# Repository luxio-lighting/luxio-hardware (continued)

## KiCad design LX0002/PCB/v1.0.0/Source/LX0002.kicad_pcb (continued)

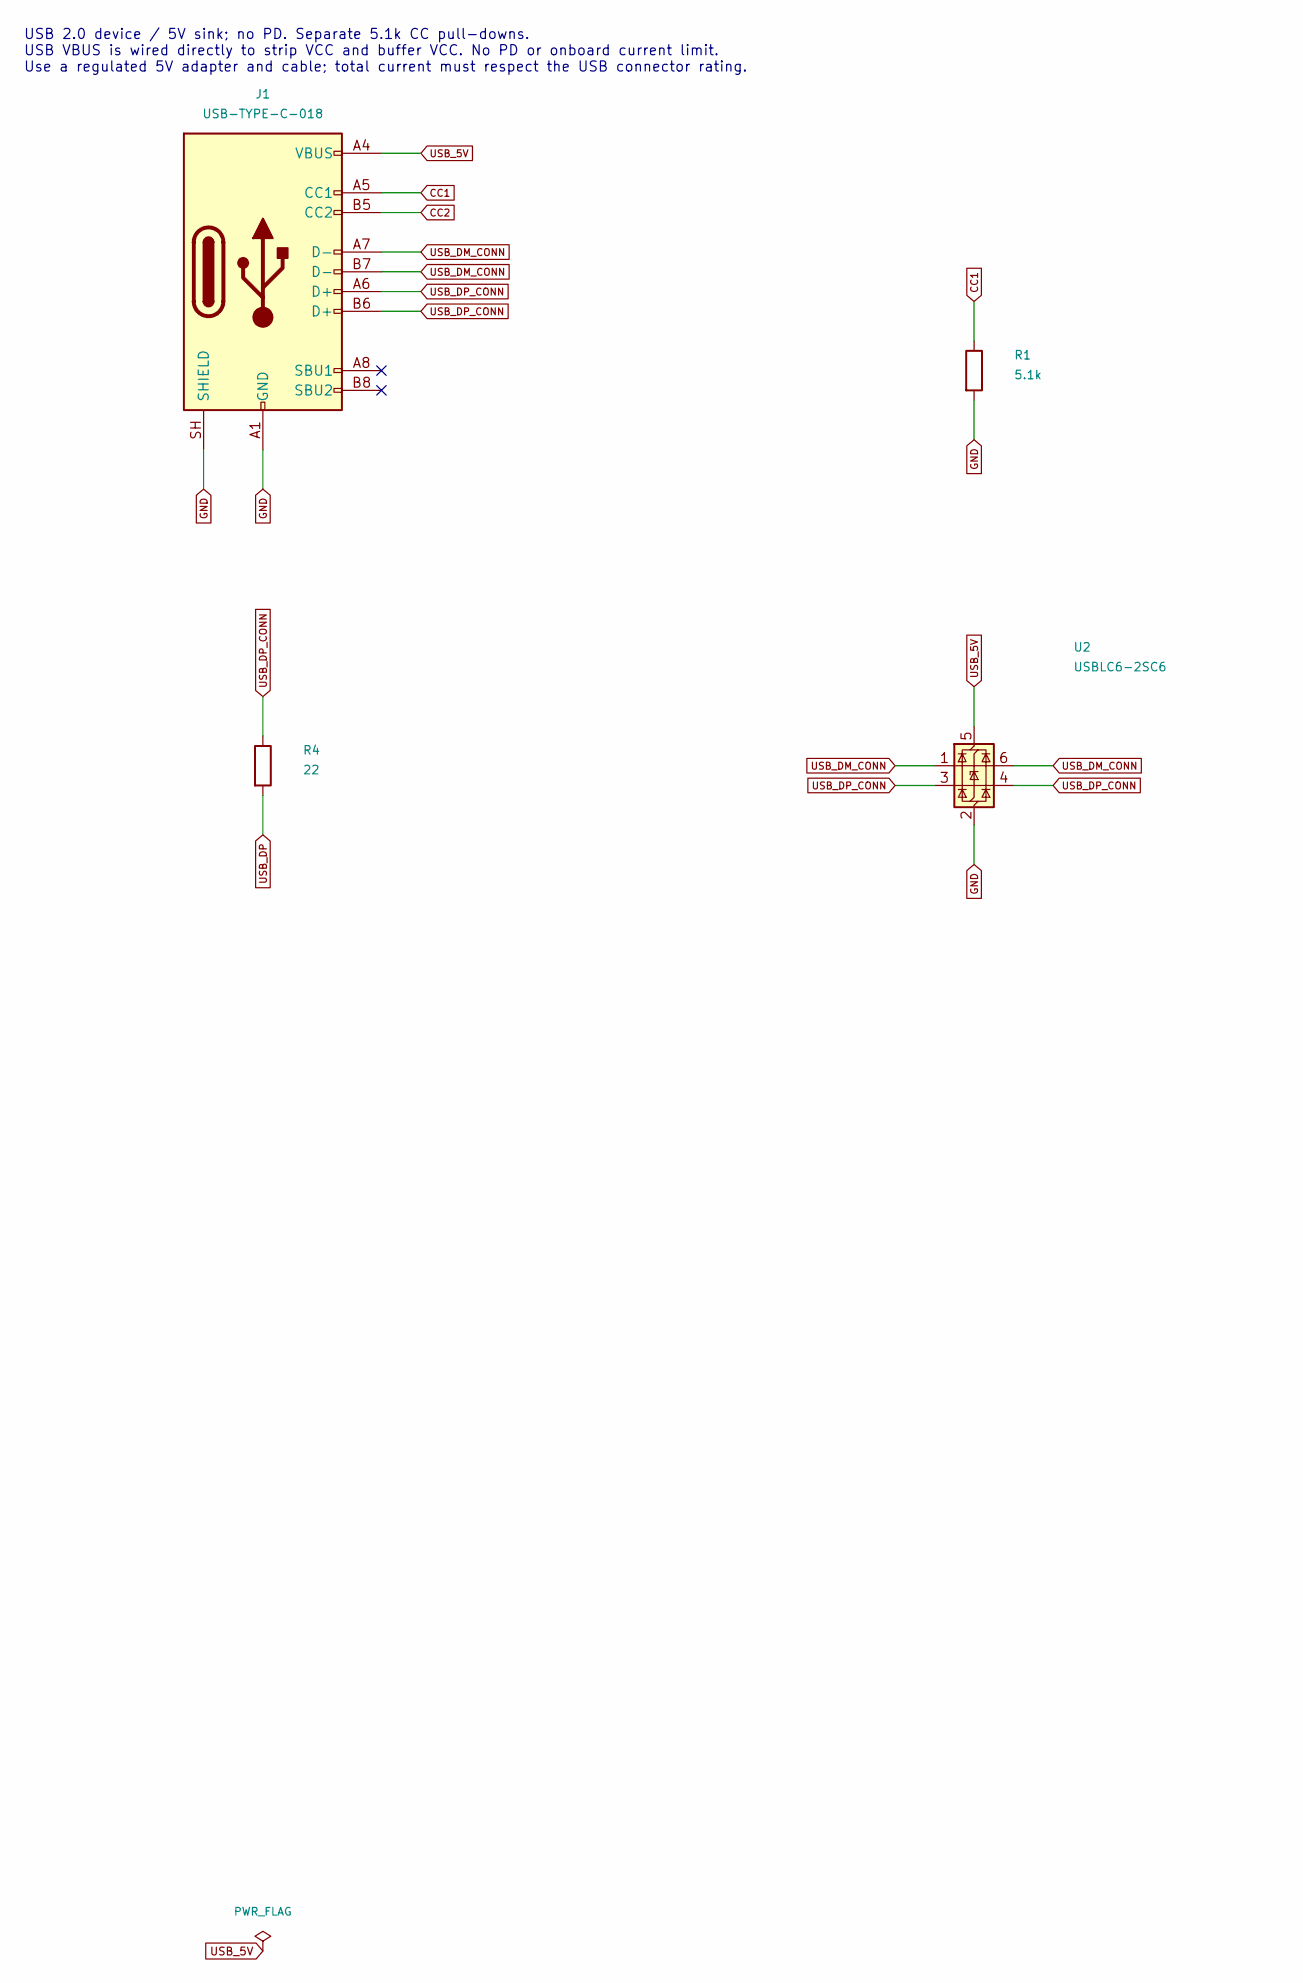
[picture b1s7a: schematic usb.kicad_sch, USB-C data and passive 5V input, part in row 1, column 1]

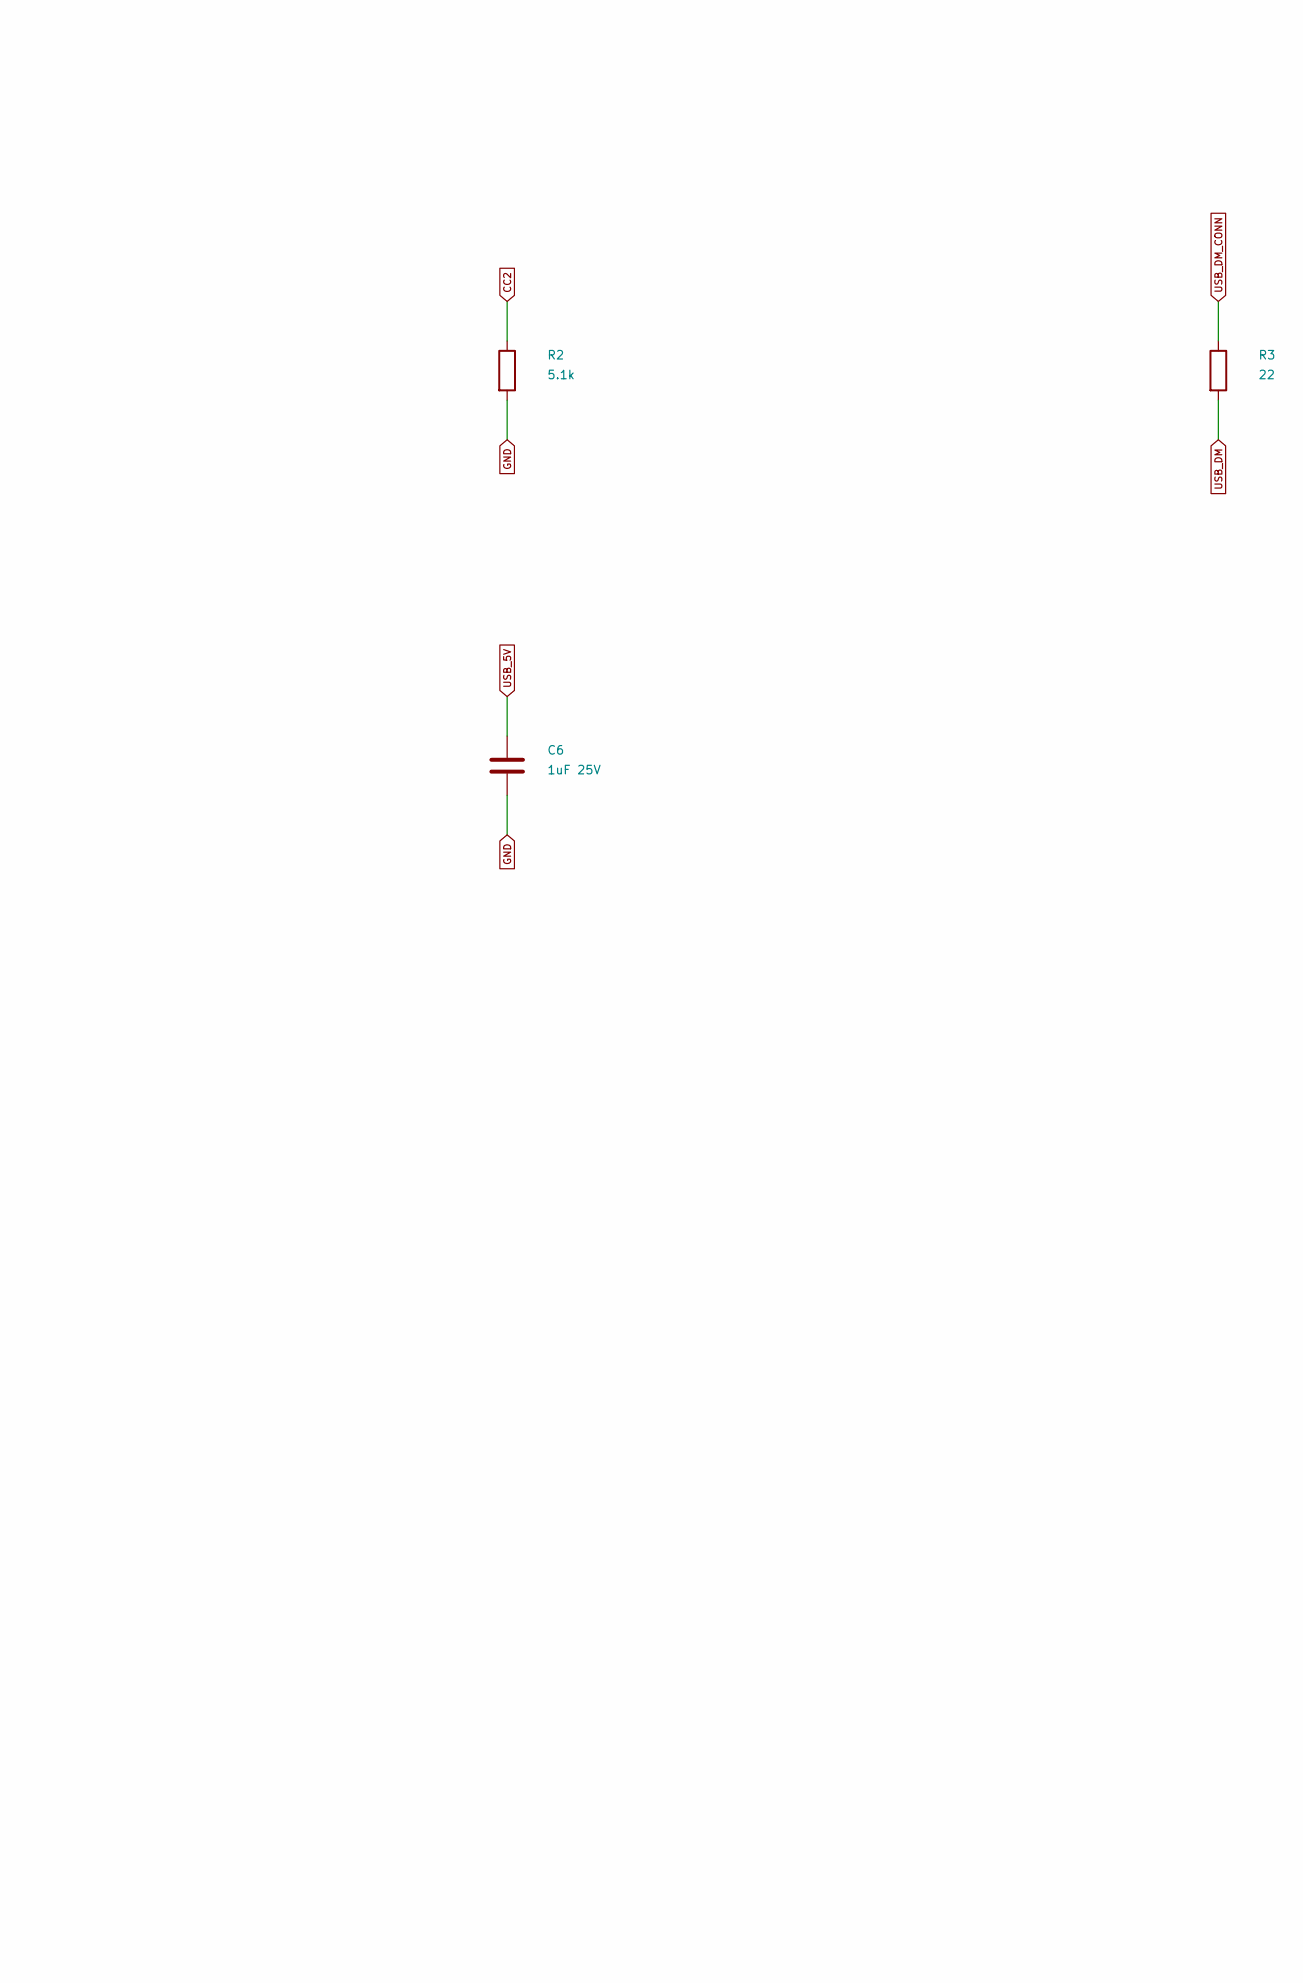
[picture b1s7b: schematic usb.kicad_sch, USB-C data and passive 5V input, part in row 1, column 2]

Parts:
C6: 1uF 25V; C_0402_1005Metric; LCSC C52923
J1: USB-TYPE-C-018; USB_C_DEALON_USB_TYPE_C_018; LCSC C2927038
R1, R2: 5.1k; R_0402_1005Metric; LCSC C25905
R3, R4: 22; R_0402_1005Metric; LCSC C25092
U2: USBLC6-2SC6; SOT-23-6; LCSC C7519

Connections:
CC1: J1.A5 (CC1), R1.1
CC2: J1.B5 (CC2), R2.1
GND: C6.2, J1.A1 (GND), J1.A12 (GND), J1.B1 (GND), J1.B12 (GND), J1.SH (SHIELD), R1.2, R2.2, U2.2 (GND); also elsewhere on the board
USB_5V: C6.1, J1.A4 (VBUS), J1.A9 (VBUS), J1.B4 (VBUS), J1.B9 (VBUS), U2.5 (VBUS); also elsewhere on the board
USB_DM: R3.2; also elsewhere on the board
USB_DM_CONN: J1.A7 (D-), J1.B7 (D-), R3.1, U2.1 (I/O1), U2.6 (I/O1)
USB_DP: R4.2; also elsewhere on the board
USB_DP_CONN: J1.A6 (D+), J1.B6 (D+), R4.1, U2.3 (I/O2), U2.4 (I/O2)

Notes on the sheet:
USB 2.0 device / 5V sink; no PD. Separate 5.1k CC pull-downs. USB VBUS is wired directly to strip VCC and buffer VCC. No PD or onboard current limit. Use a regulated 5V adapter and cable; total current must respect the USB connector rating.

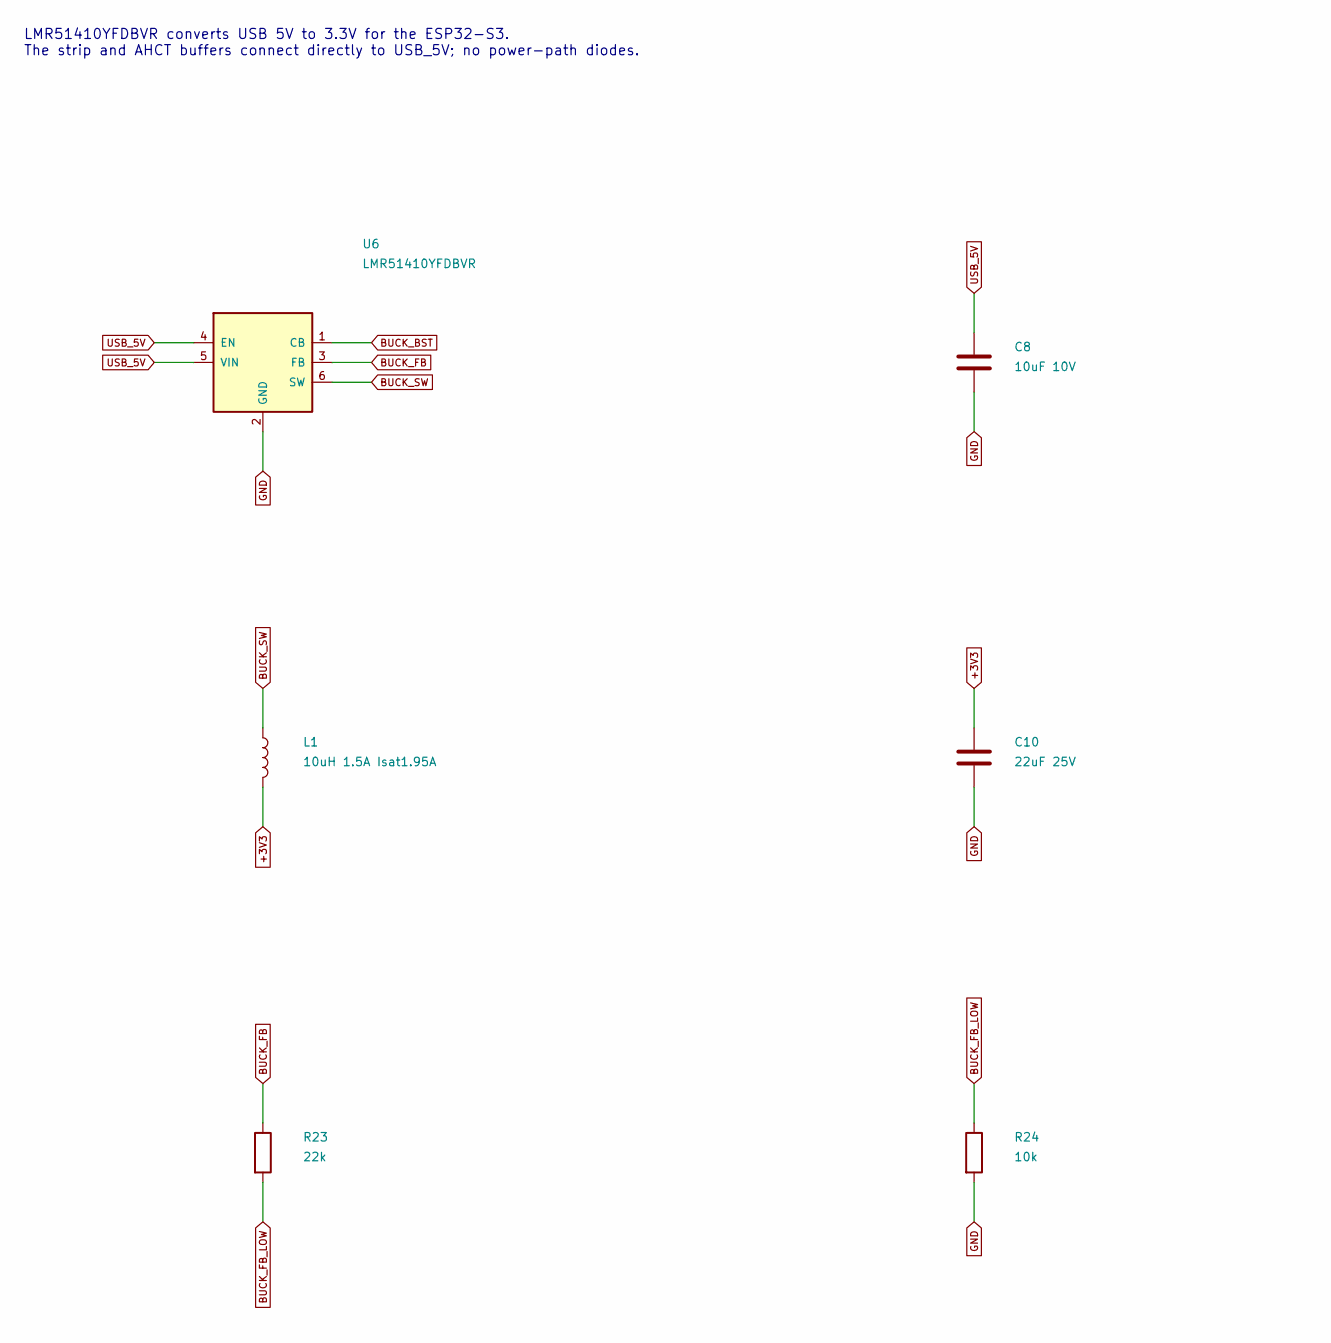
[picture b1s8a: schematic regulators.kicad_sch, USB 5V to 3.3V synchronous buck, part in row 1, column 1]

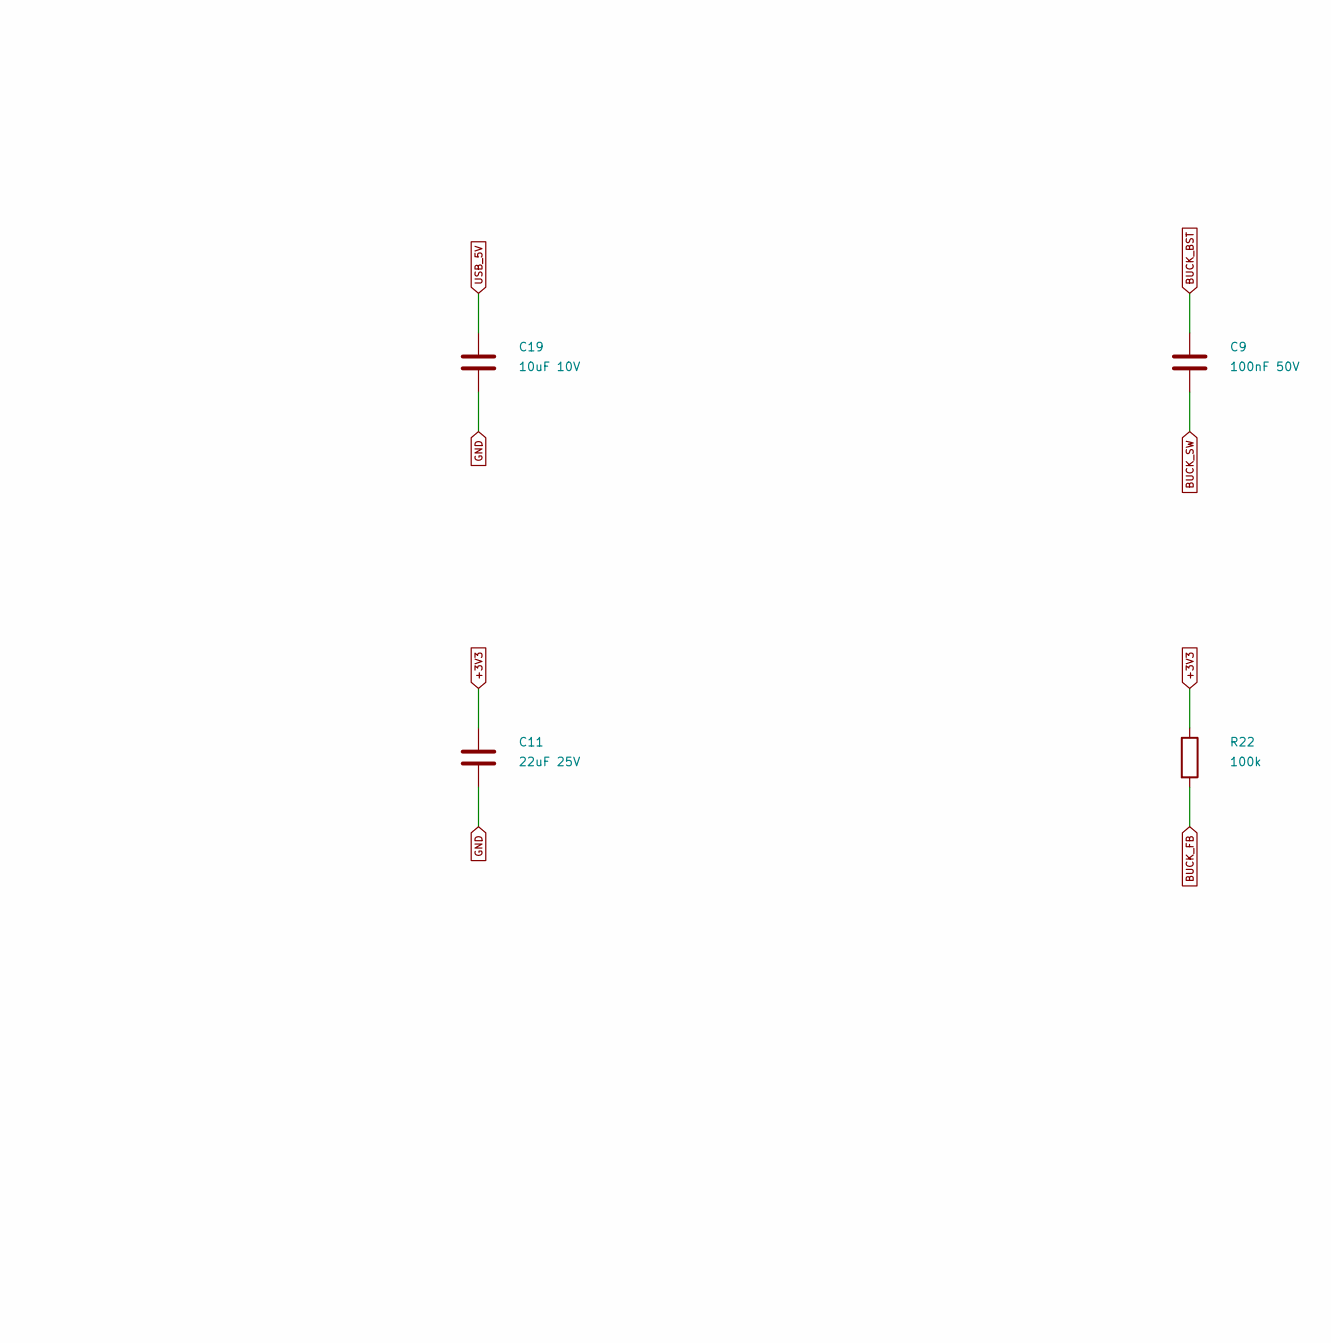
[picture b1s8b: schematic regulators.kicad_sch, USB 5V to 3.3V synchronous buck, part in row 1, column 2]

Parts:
C8, C19: 10uF 10V; C_0603_1608Metric; LCSC C19702
C9: 100nF 50V; C_0603_1608Metric; LCSC C14663
C10, C11: 22uF 25V; C_0805_2012Metric; LCSC C45783
L1: 10uH 1.5A Isat1.95A; L_Sunlord_SWPA4030S; LCSC C38117
R22: 100k; R_0402_1005Metric; LCSC C25741
R23: 22k; R_0402_1005Metric; LCSC C25768
R24: 10k; R_0402_1005Metric; LCSC C25744
U6: LMR51410YFDBVR; SOT-23-6; LCSC C32347484

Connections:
+3V3: C10.1, C11.1, L1.2, R22.1; also elsewhere on the board
BUCK_BST: C9.1, U6.1 (CB)
BUCK_FB: R22.2, R23.1, U6.3 (FB)
BUCK_FB_LOW: R23.2, R24.1
BUCK_SW: C9.2, L1.1, U6.6 (SW)
GND: C8.2, C10.2, C11.2, C19.2, R24.2, U6.2 (GND); also elsewhere on the board
USB_5V: C8.1, C19.1, U6.4 (EN), U6.5 (VIN); also elsewhere on the board

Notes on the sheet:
LMR51410YFDBVR converts USB 5V to 3.3V for the ESP32-S3. The strip and AHCT buffers connect directly to USB_5V; no power-path diodes.

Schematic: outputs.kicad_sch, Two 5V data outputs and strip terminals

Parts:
C14, C17: 100nF 50V; C_0603_1608Metric; LCSC C14663
J3, J4: 2060-452-HDGC; HDGC_2060_452; LCSC C55251566
R16, R27: 100; R_0603_1608Metric; LCSC C22775
R18, R29: 100k; R_0603_1608Metric; LCSC C25803
U8, U9: SN74AHCT1G125DBVR; SOT-23-5; LCSC C7484

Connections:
DATA16_5V: R16.1, U8.4
DATA16_OUT: J3.1, R16.2
DATA17_5V: R27.1, U9.4
DATA17_OUT: J4.2, R27.2
GND: C14.2, C17.2, J3.2, R18.2, R29.2, U8.1, U8.3 (GND), U9.1, U9.3 (GND); also elsewhere on the board
GPIO16: R18.1, U8.2; also elsewhere on the board
GPIO17: R29.1, U9.2; also elsewhere on the board
USB_5V: C14.1, C17.1, J4.1, U8.5 (VCC), U9.5 (VCC); also elsewhere on the board

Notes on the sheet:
GPIO16 / GPIO17 -> AHCT buffers -> 100-ohm series resistors. Buffers always enabled in hardware; 100k input pull-downs hold data low during reset.

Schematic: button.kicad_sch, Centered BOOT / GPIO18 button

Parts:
D4: BAT54C; SOT-23; LCSC C2135
R30: 10k; R_0402_1005Metric; LCSC C25744
SW1: TS-1088-AR02016; SW_TS-1088-AR02016; LCSC C720477

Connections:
+3V3: R30.1; also elsewhere on the board
BOOT: D4.1; also elsewhere on the board
BUTTON_COMMON: D4.3, SW1.1
GND: SW1.2; also elsewhere on the board
GPIO18_BUTTON: D4.2, R30.2; also elsewhere on the board

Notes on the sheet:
SW1 pulls BOOT and GPIO18 low through separate Schottky diodes. Firmware uses GPIO18 as an input. BOOT must be held low during reset for download.

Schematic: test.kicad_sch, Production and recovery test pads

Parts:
TP1: GND; TestPoint_Pad_D1.0mm
TP2: +3V3; TestPoint_Pad_D1.0mm
TP3: ESP_EN; TestPoint_Pad_D0.5mm
TP6: GPIO16; TestPoint_Pad_D1.0mm
TP7: GPIO17; TestPoint_Pad_D1.0mm
TP8, TP9: USB_5V; TestPoint_Pad_D1.0mm
TP10: GPIO18_BUTTON; TestPoint_Pad_D1.0mm

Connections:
+3V3: TP2.1; also elsewhere on the board
ESP_EN: TP3.1; also elsewhere on the board
GND: TP1.1; also elsewhere on the board
GPIO16: TP6.1; also elsewhere on the board
GPIO17: TP7.1; also elsewhere on the board
GPIO18_BUTTON: TP10.1; also elsewhere on the board
USB_5V: TP8.1, TP9.1; also elsewhere on the board

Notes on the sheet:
Test-point map for recovery, power rails and data. Use common ground. Data buffers are always enabled; no power-control GPIOs.

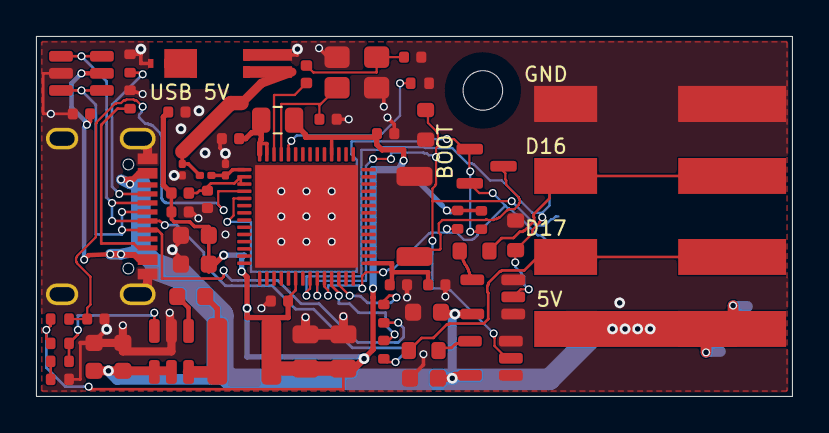
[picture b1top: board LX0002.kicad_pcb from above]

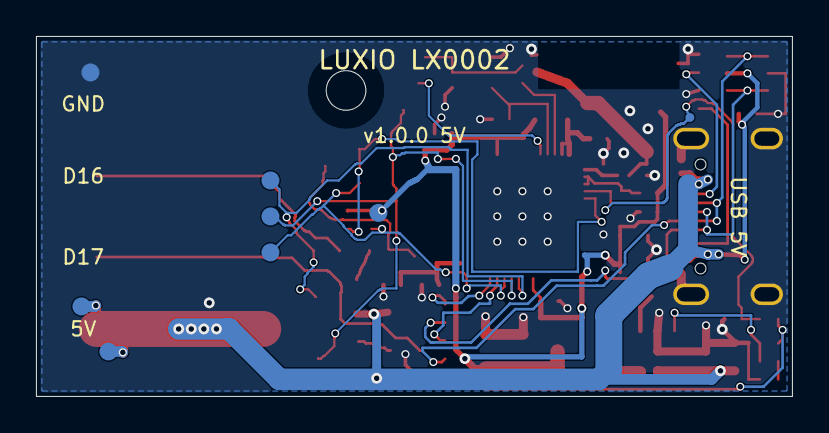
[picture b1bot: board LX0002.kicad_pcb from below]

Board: 2 copper layers, 42.0 x 20.0 mm, 65 parts (8 on the bottom side), 33 nets.

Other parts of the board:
H2: MountingHole_2.2mm_M2

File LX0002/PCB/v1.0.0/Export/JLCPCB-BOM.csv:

Comment,Designator,Footprint,LCSC Part #,Quantity
RFECA3216060A1T,ANT1,Core:Walsin_RFECA3216060A1T_Type1,C127620,1
100nF 50V,"C14,C17,C9",Capacitor_SMD:C_0603_1608Metric,C14663,3
100nF 16V,"C101,C102,C103,C104,C105,C108",Capacitor_SMD:C_0402_1005Metric,C1525,6
18pF 50V C0G,"C112,C113",Capacitor_SMD:C_0402_1005Metric,C1549,2
1.5pF 50V C0G,"C114,C115",Capacitor_SMD:C_0201_0603Metric,C161414,2
0,R106,Resistor_SMD:R_0805_2012Metric,C17477,1
2nH 900mA,L100,Inductor_SMD:L_0402_1005Metric,C18216,1
10uF 10V,"C100,C107,C19,C8",Capacitor_SMD:C_0603_1608Metric,C19702,4
BAT54C,D4,Package_TO_SOT_SMD:SOT-23,C2135,1
100,"R16,R27",Resistor_SMD:R_0603_1608Metric,C22775,2
22,"R3,R4",Resistor_SMD:R_0402_1005Metric,C25092,2
100k,R22,Resistor_SMD:R_0402_1005Metric,C25741,1
10k,"R100,R101,R103,R24,R30",Resistor_SMD:R_0402_1005Metric,C25744,5
22k,R23,Resistor_SMD:R_0402_1005Metric,C25768,1
100k,"R18,R29",Resistor_SMD:R_0603_1608Metric,C25803,2
5.1k,"R1,R2",Resistor_SMD:R_0402_1005Metric,C25905,2
USB-TYPE-C-018,J1,LX0002:USB_C_DEALON_USB_TYPE_C_018,C2927038,1
ESP32-S3FH4R2,U1,Core:ESP32_S3FH4R2_QFN56_7x7_EP5p7,C3013940,1
LMR51410YFDBVR,U6,Package_TO_SOT_SMD:SOT-23-6,C32347484,1
10uH 1.5A Isat1.95A,L1,Inductor_SMD:L_Sunlord_SWPA4030S,C38117,1
22uF 25V,"C10,C11",Capacitor_SMD:C_0805_2012Metric,C45783,2
1uF 25V,"C106,C109,C111,C6",Capacitor_SMD:C_0402_1005Metric,C52923,4
2060-452-HDGC,"J3,J4",LX0002:HDGC_2060_452,C55251566,2
40MHz 12pF 10ppm,Y1,Crystal:Crystal_SMD_3225-4Pin_3.2x2.5mm,C655034,1
TS-1088-AR02016,SW1,LX0002:SW_TS-1088-AR02016,C720477,1
2.7nH,L102,Inductor_SMD:L_0201_0603Metric,C7216765,1
SN74AHCT1G125DBVR,"U8,U9",Package_TO_SOT_SMD:SOT-23-5,C7484,2
USBLC6-2SC6,U2,Package_TO_SOT_SMD:SOT-23-6,C7519,1
24nH,L101,Inductor_SMD:L_0402_1005Metric,C913699,1

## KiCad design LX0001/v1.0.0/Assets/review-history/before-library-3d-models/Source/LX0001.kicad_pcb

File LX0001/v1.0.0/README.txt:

LX0001 v1.0.0 — Luxio digital LED-strip controller

CURRENT STATUS: Four-layer fabrication data checked; first article not yet built.
Zero unrouted connections, zero schematic parity issues and zero ERC findings.
Four documented mechanical flags concern the recessed USB shell stakes.

Open Source/LX0001.kicad_pro in KiCad 10. The schematic and PCB are editable;
their symbol and footprint libraries are included in Source/libraries.
Custom connector/antenna 3D bodies are approximate preview models. Use the
manufacturer drawings, not the simplified bodies, for enclosure tolerances.

Design
60 x 20 mm, four copper layers, 1.6 mm FR-4, black mask and white silkscreen.
Bare ESP32-S3, 4 MB external flash, no PSRAM, ceramic 2.4 GHz edge antenna.
Two AHCT buffers translate GPIO16 and GPIO17 to 5 V data outputs.
The input terminal and underside USB-C share the end's y=10 mm centerline.
The two output terminals are centered as a pair at the opposite end.
The BOOT/GPIO18 button is centered at (30,10) mm. Two 2.2 mm M2 holes provide
case mounting; their centers are (9,17) and (42,3) mm from the top-left corner.

Connections, viewed from the top with the input at the left
Input, from antenna-side edge toward the opposite edge: GND, 5-24 V.
Output in the same direction: GND, GPIO16/5 V logic, GPIO17/5 V logic, VCC.
VCC follows the selected supply. It is not converted to the strip's voltage.
The design target is 5 A continuous from the wired supply, including 24 V/120 W.
An 8 A fuse provides fault protection; it is not a precise 5 A current limiter.

A powered wired input takes hardware priority over USB and enables strip power.
USB data stays connected. USB-only operation provides 5 V and has a shared
controller/strip current limit: approximately 0.44 A or 1.28 A, selected by
firmware only when the source permits it. USB strip power defaults OFF.
Firmware must enable it for a configured 5 V strip and enforce the remaining
current budget. A 12/24 V strip requires a suitable wired supply. The circuit
cannot identify a strip's rated voltage from its wires. No firmware is supplied.
See Source/firmware-interface.txt for the complete GPIO and startup contract.

Files
Source: native KiCad project, local libraries, connection table, design notes,
firmware interface and reproducible authoring/checking tools.
Assets: manufacturer datasheets, mechanical drawings, sourcing evidence and
the documented local routing-tool patch.
Export: schematic PDF, JLCPCB BOM/CPL, Gerber/drill archive, assembly drawings,
3D previews and verification reports. Manufacturing files are generated only
after the release checks in Source/tools/export_manufacturing.py pass.

Fabrication/assembly intent
Two-sided assembly, 1 oz outer / 0.5 oz inner copper, ENIG, 1.6 mm and black mask.
Order JLC04161H-7628 stackup; preserve the documented RF geometry.
Use JLCPCB standard two-side PCBA with assembler-designed panel rails/fiducials.
The GCT USB shell stakes are recessed inside the board. Four courtyard flags
refer to their annuli near the opposite-side terminal; top annuli are masked.
Prevent top-side solder protrusions and inspect this overlap on first articles.
See Source/fabrication-intent.txt and the exact connector drawing/notes.
Review the live JLCPCB placement preview and rotations before submitting an
order. No board order has been placed by this task.

Engineering status
The board has not been built or measured. CAD verification does not qualify
5 A thermal performance, antenna matching, USB behavior or assembly yield.
Build and test first articles using Source/first-article-validation.txt before
releasing the 100-board lot. Export/verification.json records the final CAD
checks when available; Source/current_path_review.txt separates copper modeling
from measured thermal performance. Initial RF matching requires measurement.

Cost snapshot, 2026-11-11
109 purchased placements, 52 unique purchased parts, one DNP tuning position
and 11 bare test pads. Components total approximately USD13.3690 per board or
USD1,336.90 per100, excluding PCB, assembly, setup, attrition, tax and shipping.
The dated component-price/stock evidence is not a reservation or a JLCPCB quote.

Editing/rebuilding
Native KiCad files are the primary editable deliverables. Running generate.py
without --board rebuilds only schematic/connection data. Running it with
--board REPLACES the PCB with initial placement and removes completed routing.
Do not run it on a manually revised routed board without preserving that work.

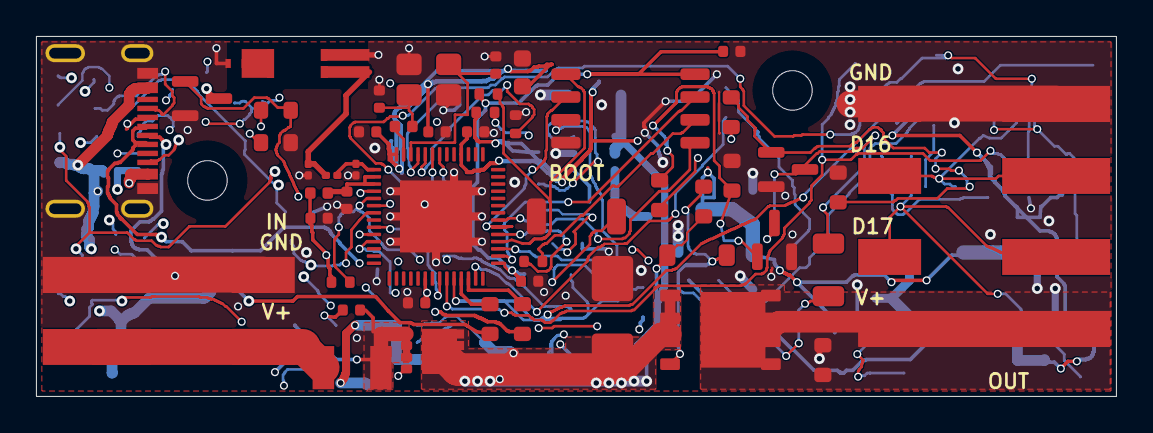
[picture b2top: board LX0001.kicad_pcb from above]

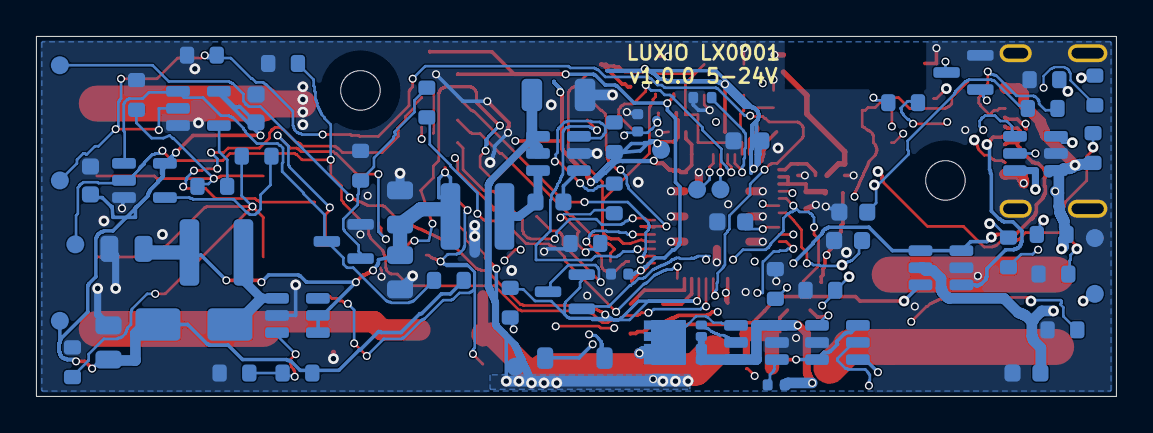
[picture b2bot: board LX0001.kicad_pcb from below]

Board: 4 copper layers, 60.0 x 20.0 mm, 123 parts (70 on the bottom side), 73 nets.

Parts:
ANT1: RFECA3216060A1T; Walsin_RFECA3216060A1T_Type1
C4, C9, C14, C15, C16, C17: 100nF 50V; C_0603_1608Metric
C5, C7: 100nF 50V; C_0402_1005Metric
C6: 1uF 50V; C_0603_1608Metric
C8: 10uF 50V; C_1206_3216Metric
C10, C11, C12, C13: 22uF 25V; C_0805_2012Metric
C100, C107: 10uF 10V; C_0603_1608Metric
C101, C102, C103, C104, C105, C108, C110: 100nF 16V; C_0402_1005Metric
C106, C109, C111: 1uF 25V; C_0402_1005Metric
C112, C113: 18pF 50V C0G; C_0402_1005Metric
C114, C115: 1.5pF 50V C0G; C_0201_0603Metric
D1: 1N4148W; D_SOD-123
D2: SS14; D_SMA
D3: SMBJ24A; D_SMB
D4: BAT54C; SOT-23
D5: BZT52C12; D_SOD-123
F1: 8A 32V; Fuse_SART_S1206_FA
H1, H2: MountingHole_2.2mm_M2
J1: USB4215-03-A; USB_C_GCT_USB4215_03_A
J2, J3, J4: 2060-452-HDGC; HDGC_2060_452
L1: 10uH 1.5A Isat1.95A; L_Sunlord_SWPA4030S
L2: 4.7uH 2A Isat2.9A; L_Sunlord_SWPA4030S
L100: 2nH 900mA; L_0402_1005Metric
L101: 24nH; L_0402_1005Metric
L102: 2.7nH; L_0201_0603Metric
L104: DNP 0R antenna tune; Walsin_RFECA_Tuner_0402
Q1, Q3: CSD18543Q3A; VSON-8_3.3x3.3mm_P0.65mm_NexFET
Q2, Q4: MMBT3904; SOT-23
Q5: 2N7002; SOT-23
Q6: CMSA80P06A; CMSA80P06A_DFN5x6
Q7, Q8: MMBT5551; SOT-23
R1, R2: 5.1k; R_0603_1608Metric
R3, R4: 22; R_0603_1608Metric
R8, R10, R13, R17, R18, R20, R22, R25, R26, R28, R29, R33, R34, R37, R39, R40: 100k; R_0603_1608Metric
R9: 150k; R_0603_1608Metric
R11, R31, R32: 30.1k 1%; R_0603_1608Metric
R12: 47k; R_0603_1608Metric
R14: 73.2k; R_0603_1608Metric
R15, R19, R21, R24, R30, R36, R38: 10k; R_0603_1608Metric
R16, R27: 100; R_0603_1608Metric
R23: 22k; R_0603_1608Metric
R35: 2.2k 0.25W; R_1206_3216Metric
R100, R101, R102, R103, R110: 10k; R_0402_1005Metric
R105: 0; R_0402_1005Metric
SW1: TS-1088-AR02016; SW_TS-1088-AR02016
TP1: GND; TestPoint_Pad_D1.0mm
TP2: +3V3; TestPoint_Pad_D1.0mm
TP3: ESP_EN; TestPoint_Pad_D0.5mm
TP5: USB_FAULT; TestPoint_Pad_D1.0mm
TP6: GPIO16; TestPoint_Pad_D1.0mm
TP7: GPIO17; TestPoint_Pad_D1.0mm
TP8: +5V_DATA; TestPoint_Pad_D1.0mm
TP9: VSYS; TestPoint_Pad_D1.0mm
TP10: GPIO18_BUTTON; TestPoint_Pad_D1.0mm
TP11: UART_TX; TestPoint_Pad_D1.0mm
TP12: UART_RX; TestPoint_Pad_D1.0mm
U1: ESP32-S3; QFN-56-1EP_7x7mm_P0.4mm_EP4x4mm
U2: USBLC6-2SC6; SOT-23-6
U3, U5: LM74700QDBVRQ1; SOT-23-6
U4: TPS2553DBVR; SOT-23-6
U6: LMR51410YFDBVR; SOT-23-6
U7: MT3608; SOT-23-6
U8, U9: SN74AHCT1G125DBVR; SOT-23-5
U10: W25Q32JVSSIQ; SOIC-8_5.3x5.3mm_P1.27mm
Y1: 40MHz 12pF 10ppm; Crystal_SMD_3225-4Pin_3.2x2.5mm

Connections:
+3V3: C10.1, C11.1, C12.1, C100.1, C101.1, C103.1, C104.1, C105.1, C106.1, C107.1, L1.2, L2.1, L100.1, R22.1, R30.1, R100.1, R101.1, TP2.1, U1.20, U1.46, U1.55, U1.56, U7.4, U7.5
+5V_DATA: C13.1, C14.1, C17.1, D2.1, R14.1, R21.1, TP8.1, U8.5, U9.5
ANT_TUNE: ANT1.2, L104.1
BOOST_FB: R14.2, R15.1, U7.3
BOOST_SW: D2.2, L2.2, U7.1
BOOT: D4.1, R101.2, U1.5
BUCK_BST: C9.1, U6.1
BUCK_FB: R22.2, R23.1, U6.3
BUCK_FB_LOW: R23.2, R24.1
BUCK_SW: C9.2, L1.1, U6.6
BUTTON_COMMON: D4.3, SW1.1
CC1: J1.A5, R1.1, R25.1
CC1_SENSE: C15.1, R25.2, U1.6
CC2: J1.B5, R2.1, R26.1
CC2_SENSE: C16.1, R26.2, U1.7
DATA16_5V: R16.1, U8.4
DATA16_OUT: J3.1, R16.2, R17.1
DATA17_5V: R27.1, U9.4
DATA17_OUT: J4.2, R27.2, R28.1
DATA_ENABLE: R19.1, U1.27
DATA_ENABLE_B: Q4.1, R19.2, R20.1
DATA_OE_N: Q4.3, R21.2, U8.1, U9.1
DC_FUSED: C5.2, D1.2, F1.2, Q1.1, Q1.2, Q1.3, U3.3, U3.6
DC_GATE: Q1.4, U3.5
DC_IN: F1.1, J2.2
DC_SENSE_B: Q2.1, R12.2, R13.1
DC_SENSE_R: D1.1, R12.1, R38.1
DC_VCAP: C5.1, U3.1
ESP_EN: C111.1, R100.2, TP3.1, U1.4
FLASH_CLK: R105.2, U10.6
FLASH_CS: R110.2, U1.32, U10.1
FLASH_IO0: U1.35, U10.5
FLASH_IO1: U1.34, U10.2
FLASH_IO2: U1.31, U10.3
FLASH_IO3: U1.30, U10.7
GND: ANT1.3, C4.2, C6.2, C8.2, C10.2, C11.2, C12.2, C13.2, C14.2, C15.2, C16.2, C17.2, C100.2, C101.2, C102.2, C103.2, C104.2, C105.2, C106.2, C107.2, C108.2, C109.2, C110.2, C111.2, C112.2, C113.2, C114.2, C115.2, D3.2, J1.A1, J1.A12, J1.B1, J1.B12, J1.SH, J2.1, J3.2, L104.2, Q2.2, Q4.2, Q5.2, Q7.2, Q8.2, R1.2, R2.2, R9.2, R13.2, R15.2, R17.2, R18.2, R20.2, R24.2, R28.2, R29.2, R31.2, R33.2, R37.2, R39.2, R40.2, R102.2, R103.2, SW1.2, TP1.1, U1.57, U2.2, U3.2, U4.2, U5.2, U6.2, U7.2, U8.3, U9.3, U10.4, Y1.2, Y1.4
GPIO16: R18.1, TP6.1, U1.22, U8.2
GPIO17: R29.1, TP7.1, U1.23, U9.2
GPIO18_BUTTON: D4.2, R30.2, TP10.1, U1.24
LED_VCC: J4.1, Q6.5, R40.1
RF_50: ANT1.1, C115.1, L102.2
RF_CHIP: C114.1, L102.1, U1.1
SPICLK: R105.1, U1.33
STRAP45: R102.1, U1.51
STRAP46: R103.1, U1.52
STRIP_DC_BASE: Q8.1, R38.2, R39.1
STRIP_GATE: D5.2, Q6.4, R34.2, R35.1
STRIP_PULLDOWN: Q7.3, Q8.3, R35.2
STRIP_USB_BASE: Q7.1, R36.2, R37.1
UART_RX: TP12.1, U1.50
UART_TX: TP11.1, U1.49
USB_5V: C6.1, J1.A4, J1.A9, J1.B4, J1.B9, R8.1, R10.1, U2.5, U4.1
USB_DM: R3.2, U1.25
USB_DM_CONN: J1.A7, J1.B7, R3.1, U2.1, U2.6
USB_DP: R4.2, U1.26
USB_DP_CONN: J1.A6, J1.B6, R4.1, U2.3, U2.4
USB_ENABLE: Q2.3, R10.2, U4.3
USB_FAULT: TP5.1, U4.4
USB_GATE: Q3.4, U5.5
USB_HIGH_CURRENT: Q5.1, R33.1, U1.11
USB_ILIM: R11.1, R32.1, U4.5
USB_ILIM_HIGH: Q5.3, R32.2
USB_ILIM_MID: R11.2, R31.1
USB_LIMITED: C7.2, Q3.1, Q3.2, Q3.3, U4.6, U5.3, U5.6
USB_STRIP_EN: R36.1, U1.10
USB_VCAP: C7.1, U5.1
VBUS_SENSE: C4.1, R8.2, R9.1, U1.9
VDD3P3_RF: C102.1, L100.2, U1.2, U1.3
VDD_SPI: C108.1, C109.1, C110.1, R110.1, U1.29, U10.8
VSYS: C8.1, D3.1, D5.1, Q1.5, Q3.5, Q6.1, Q6.2, Q6.3, R34.1, TP9.1, U3.4, U5.4, U6.4, U6.5
XTAL_N: C113.1, U1.53, Y1.3
XTAL_P: L101.1, U1.54
XTAL_P_CRYSTAL: C112.1, L101.2, Y1.1

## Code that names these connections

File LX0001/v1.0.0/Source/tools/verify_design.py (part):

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      for a in pads:
       if a.GetNetname()!=net:errors.append(f'{ref}.{pin} PCB {a.GetNetname()}, expected {net}')
    byref={v['ref']:v for v in parts};u=byref['U1']['pins']
    for pin,net in {'5':'BOOT','22':'GPIO16','23':'GPIO17','24':'GPIO18_BUTTON','25':'USB_DM','26':'USB_DP','29':'VDD_SPI','57':'GND'}.items():
     if u.get(pin)!=net:errors.append('ESP32 physical pin mapping incorrect '+pin)
    assert byref['U10']['value']=='W25Q32JVSSIQ' and byref['U1']['value']=='ESP32-S3'
    assert byref['D4']['pins']=={'1':'BOOT','2':'GPIO18_BUTTON','3':'BUTTON_COMMON'}
    assert byref['J2']['pins']=={'1':'GND','2':'DC_IN'}
    assert byref['J3']['pins']=={'1':'DATA16_OUT','2':'GND'}
    assert byref['J4']['pins']=={'1':'VSYS','2':'DATA17_OUT'}
    assert all(pin not in u for pin in ['6','7','9','10','11','27'])
    assert byref['U4']['value']=='TPS22965DSGR'
    assert byref['U4']['pins']=={'1':'USB_5V','2':'USB_5V','3':'USB_ENABLE','4':'USB_5V','5':'GND','6':'USB_SLEW','7':'USB_SWITCHED','8':'USB_SWITCHED','9':'GND'}
    assert byref['U8']['pins']['1']=='GND' and byref['U9']['pins']['1']=='GND'
    assert not ({'Q4','Q5','Q6','Q7','Q8'} & set(byref))
    assert byref['R1']['pins']=={'1':'CC1','2':'GND'} and byref['R2']['pins']=={'1':'CC2','2':'GND'}
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
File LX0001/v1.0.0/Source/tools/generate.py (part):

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        r=p['ref']
        p['group']='mcu' if r=='U1' else 'rf' if r in ['ANT1','C114','C115','C116','L102','L103','L104'] else 'flash' if r=='U10' or r in ['C108','C109','C110'] or (r.startswith('R1') and int(r[1:])>=104) else 'core'
    if p['ref']=='J2':p['place']=[6.5,10,270]
    if p['ref']=='J3':p['place']=[53.5,5.75,90];p['pins']={'1':'DATA16_OUT','2':'GND'}
    if p['ref']=='J4':p['place']=[53.5,14.25,90];p['pins']={'1':'VSYS','2':'DATA17_OUT'}
placement=json.loads((HW/'placement.json').read_text()) if (HW/'placement.json').exists() else {}
for p in parts:
    if p['ref'] in placement:
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flag=symbol('power','PWR_FLAG');flag[1]=q('power:PWR_FLAG');cache['power:PWR_FLAG']=flag
rootid=uid('schematic')
group_info={
 'mcu':('ESP32-S3 / no PSRAM',['GND'], 'Bare ESP32-S3, 4 MB external quad-SPI flash. GPIO16 / GPIO17 drive 5 V buffers.\nGPIO18 senses the shared BOOT button through an isolation diode.'),
 'core':('MCU power, straps and 40 MHz clock',['+3V3','VDD3P3_RF'], '3.3 V power, local bypassing, boot straps and 40 MHz crystal.\nGPIO45 and GPIO46 pulled LOW. Boot recovery: hold SW1 and pulse EN low.'),
 'flash':('4 MB flash and SPI termination',['VDD_SPI'], 'W25Q32JVSSIQ, 32 Mbit = 4 MB, no PSRAM.\nVDD_SPI is the ESP32 flash supply. R105 reserves clock-series tuning.'),
 'rf':('2.4 GHz ceramic antenna and RF matching',[], 'Walsin RFECA3216060A1T. Preserve the 8 x 3 mm edge clearance on ALL copper layers.\nRF matching values are initial values; tune on assembled PCB in final enclosure.'),
 'usb':('USB-C data and passive 5 V input',['USB_5V'], 'USB 2.0 device / 5 V sink; no PD. Separate 5.1k CC pull-downs.\nNo current negotiation or onboard USB current limiter; use a suitably rated 5 V adapter.'),
 'power':('Automatic wired priority',['DC_FUSED','VSYS'], '5-24 V regulated wired supply has hardware priority over USB.\nReverse-blocking paths isolate sources. Design target 5 A continuous wired output.'),
 'regulators':('3.3 V buck and 5 V logic boost',['+5V_DATA'], '3.3 V buck from VSYS; boost 3.3 V to 4.99 V for AHCT buffers only.\nStrip output follows selected input voltage; no 12/24 V boost from USB.'),
 'outputs':('Two 5 V data outputs and strip terminals',[], 'GPIO16 / GPIO17 -> AHCT buffers -> 100-ohm series resistors.\nBuffers always enabled in hardware; 100k input pull-downs hold data low during reset.'),
 'button':('Centered BOOT / GPIO18 button',[], 'SW1 pulls BOOT and GPIO18 low through separate Schottky diodes.\nFirmware uses GPIO18 as an input. BOOT must be held low during reset for download.'),
 'test':('Production and recovery test pads',[], 'Test-point map for recovery, power rails and data.\nUse common ground. Power selection and data enables need no firmware control.')}
# Split larger sections across A3 pages, keeping the MCU alone for readable pin names.
groups=[]
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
